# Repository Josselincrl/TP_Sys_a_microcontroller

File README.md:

# TP_Sys_a_microcontroller
TP de système a microcontrolleur

Salut salut ! :)

################ Partie STM32 #####################

Q.13 PA9 est relié à la masse par ce que c'est le reset et afin que son etat ne sois pas flottant.

Q.14 Ces componsants servent à faire du filtrage entre la partie analogique (VA -> Vanalogique) et la partie numérique (V)

################ Partie LDO #####################
Q.1 Page 1 les condo doivent etre superieur a 0.47uF 

################ Partie DAC #####################

Q.5 Les condos sont spécifiés page 25

Q.6 Le role de la broche notCS est de choisir le chip sur lequel on travail. Dans le cas de ce compansant il met en route l'horlaoge du DAC 
"CS is the Chip Select input pin, which requires an active-low to enable serial clock and data functions."

Q.7 nLDAC permet d'activer la sortie du DAC. Cela peut etre utile pour synchroniser plusieurs DAC. Synchronization Input. This pin is used to transfer DAC settings
(Input Registers) to the output registers (VOUT)"

Q.8 MISO n'est pas utilisé car le DAC recoit unniquement des données. Aucune données vont dans l'autre sens.

################ Partie empreinte #####################

Q.3 0805 0603 sont des tailles normés de composants

Q.4 LQFP, SOT-223, SOIC sont des boitiers 

################ Partie firmware #####################
Q.2 
"The HAL offers high-level and feature-oriented APIs with a high-portability level. These hide the MCU and peripheral
complexity from the end-user.
The LL offers low-level APIs at register level, with better optimization but less portability. These require deep knowledge of
the MCU and peripheral specifications."

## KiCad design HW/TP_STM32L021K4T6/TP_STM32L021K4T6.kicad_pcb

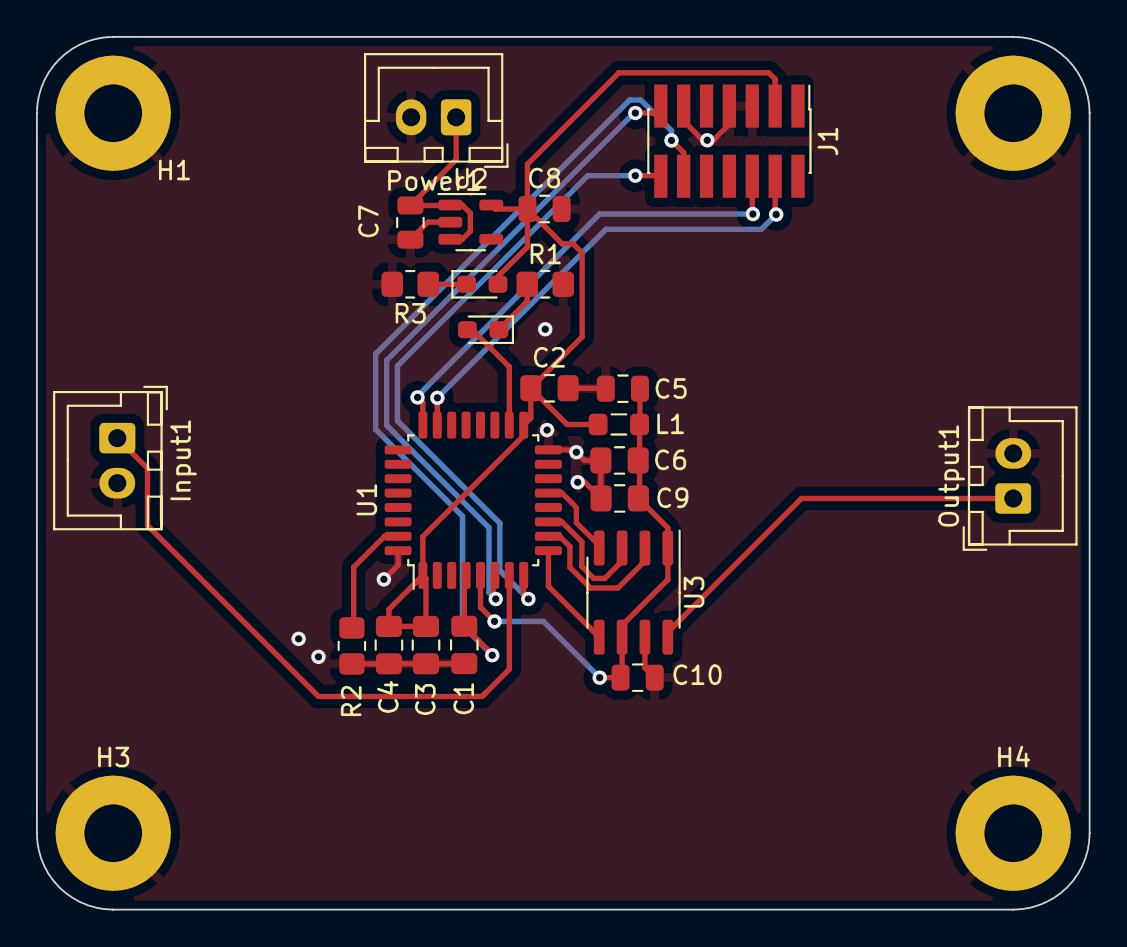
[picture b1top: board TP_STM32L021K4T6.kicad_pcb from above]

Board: 2 copper layers, 58.5 x 48.5 mm, 27 parts (0 on the bottom side), 19 nets.

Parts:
C1, C3, C4, C6, C9: 100n; C_0805_2012Metric_Pad1.18x1.45mm_HandSolder
C2: 4u7; C_0805_2012Metric_Pad1.18x1.45mm_HandSolder
C5, C7, C8: 1u; C_0805_2012Metric
C10: 10u; C_0805_2012Metric
D1, D2: LED; LED_0603_1608Metric_Pad1.05x0.95mm_HandSolder
H1, H2, H3, H4: MountingHole_Pad; MountingHole_3.2mm_M3_Pad
Input1: Conn_01x02; JST_XH_B2B-XH-A_1x02_P2.50mm_Vertical
J1: Conn_02x07_Odd_Even; PinHeader_2x07_P1.27mm_Vertical_SMD
L1: 39n; L_0805_2012Metric_Pad1.05x1.20mm_HandSolder
Output1: Conn_01x02; JST_XH_B2B-XH-A_1x02_P2.50mm_Vertical
Power1: Conn_01x02; JST_XH_B2B-XH-A_1x02_P2.50mm_Vertical
R1, R2, R3: 1k; R_0805_2012Metric_Pad1.20x1.40mm_HandSolder
U1: STM32L021K4Tx; LQFP-32_7x7mm_P0.8mm
U2: BU33SD5WG-TR; SOT-23-5
U3: MCP4801-EMC; SOIC-8_3.9x4.9mm_P1.27mm

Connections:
+3.3VA: C5.1, C6.1, C9.1, C10.1, L1.2, U1.5 (VDDA), U3.1 (Vdd), U3.6 (~SHDN)
+3V3: C2.1, C3.1, C4.1, C8.1, D2.2 (A), J1.3, L1.1, U1.1 (VDD), U1.17 (VDD), U2.5 (VOUT)
+5V: C7.1, Power1.1, U2.1 (VIN), U2.3 (~SHDN)
ADC_IN1: Input1.1, U1.7 (PA1)
DAC_OUT: Output1.1, U3.8 (Vout)
DAC_nCS: U1.10 (PA4), U3.2 (~CS)
DAC_nLDAC: U1.9 (PA3), U3.5 (~LDAC)
GND: C1.2, C2.2, C3.2, C4.2, C5.2, C6.2, C7.2, C8.2, C9.2, C10.2, H1.1, H2.1, H3.1, H4.1, Input1.2, J1.5, J1.7, J1.11, Output1.2, Power1.2, R1.2, R2.2, R3.2, U1.16 (VSS), U1.32 (VSS), U2.2 (GND), U3.7 (Vss)
LED_STATUS: D1.2 (A), U1.18 (PA8)
NRST: C1.1, J1.12, U1.4 (NRST)
unnamed: D1.1 (K), R1.1
unnamed: D2.1 (K), R3.1
unnamed: R2.1, U1.31 (PB9)
SPI1_MOSI: U1.13 (PA7), U3.4 (SDI)
SPI1_SCK: U1.11 (PA5), U3.3 (SCK)
SWDCLK: J1.6, U1.24 (PA14)
SWDIO: J1.4, U1.23 (PA13)
USART2_RX: J1.13, U1.6 (PA0)
USART2_TX: J1.14, U1.8 (PA2)

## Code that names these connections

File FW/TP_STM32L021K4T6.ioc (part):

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Mcu.Name=STM32L021K4Tx
Mcu.Package=LQFP32
Mcu.UserName=STM32L021K4Tx
PA0-CK_IN.Mode=Asynchronous
PA0-CK_IN.Signal=USART2_RX
PA1.Mode=IN1
PA1.Signal=ADC_IN1
PA13.Mode=Serial_Wire
PA13.Signal=SYS_SWDIO
PA14.Mode=Serial_Wire
PA14.Signal=SYS_SWCLK
PA2.Mode=Asynchronous
PA2.Signal=USART2_TX
PA3.GPIOParameters=GPIO_Label
PA3.GPIO_Label=DAC_nLDAC
PA3.Signal=GPIO_Output
PA4.GPIOParameters=GPIO_Label
PA4.GPIO_Label=DAC_nCS
PA4.Signal=GPIO_Output
PA5.Mode=TX_Only_Simplex_Unidirect_Master
PA5.Signal=SPI1_SCK
PA7.Mode=TX_Only_Simplex_Unidirect_Master
PA7.Signal=SPI1_MOSI
PA8.Signal=S_TIM2_CH1
RCC.HSE_VALUE=8000000
RCC.SYSCLKFreq_VALUE=32000000
RCC.SYSCLKSource=RCC_SYSCLKSOURCE_PLLCLK
board=custom

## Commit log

2024-02-09 Premier commit
2024-02-09 Pinout stm32 done
2024-02-09 Pinout LDO
2024-02-09 Save PCB
2024-03-14 firware
